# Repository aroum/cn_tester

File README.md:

# c!n tester: ProMicro-like Microcontroller Tester

## 🚀 Project Overview

The **c!n tester** is a dedicated hardware and software solution designed for automated functional testing of ProMicro-like microcontrollers (MCUs). Its primary goal is to provide a fast and reliable way to verify basic pin connectivity and functionality before deployment.

### 🚧 Current Status: Work In Progress (WIP)

The core testing logic and fundamental functionality are fully operational. However, active development is focused on improving the GUI and enhancing the overall user experience.

> [!IMPORTANT]
> **Bug Reports & Logging:**
> * **Any bug reports must be accompanied by logs.** Reports without logs cannot be diagnosed and will be closed.
> * **How to access logs:** Inside the GUI, click on the **USB connector image** at the center of the pinout visualization. This will open the log view showing real-time console outputs for both Master and Target MCUs.
> * If the application fails to start entirely, look for the `app_error.log` file created in the same directory as the executable.

## 🧱 Hardware System

The hardware consists of a custom Printed Circuit Board (PCB) housing two microcontrollers:

1. **Master MCU:** Controls the entire testing process, communicates with the host application, and manages test sequences.

2. **Target MCU:** This is the ProMicro-like microcontroller under test.

Essentially, the PCB represents a direct connection of the pins of the two microcontrollers; the same setup can be achieved using regular wires.

## 💻 Software System

**Technology Stack:**

* Python 3.10+
* PySide6 — used to create the graphical user interface (GUI).
* Nuitka — used to compile Python code into standalone executable files.
* platformio — used to compile MCU firmware.
* adafruit-nrfutil — used for flashing firmware onto microcontrollers.
* pyserial — provides communication between the computer and microcontrollers via COM ports.

All communication between the host application (software) and the MCUs is conducted via serial ports (COM ports).

Currently, there is no fully developed CLI application, but since both the Target and Master microcontrollers are connected to the computer via COM ports, you can interact with them directly using standard terminal commands.

## ⚙️ Testing Process Details

The system is designed for quick, repeatable functional checks. The Master MCU and the Target MCU communicate over dedicated lines to perform the tests.

### Test Sequence

The system uses an orchestrated handshake process to ensure reliable communication. On power-up, both MCUs send discovery messages. Once the application identifies and initializes the ports, the following sequence is performed under direct application control:

1. **Handshake & Initialization:** The application scans all COM ports (via **Auto Search** or manual selection), identifies the Master and Target, and sends an `INIT` command to synchronize them.

2. **All Pins HIGH:** The application commands both MCUs to enter the `ALL_HIGH` stage. The Target drives all pins HIGH, and the Master verifies the connectivity.

3. **All Pins LOW:** The application commands both MCUs to enter the `ALL_LOW` stage. The Target drives all pins LOW, and the Master verifies the state.

4. **Individual Pin Sequence:** The application orchestrates a per-pin sequence. It commands the Target to toggle a specific pin and then commands the Master to verify that specific pin's state. This step-by-step approach ensures maximum reliability and clear diagnostic feedback.

### Test Indicators

* **GUI Indicators:** The application provides real-time feedback for each test stage (All High, All Low, Sequence).
* **Pinout View:** A dynamic visualization shows exactly which pins passed or failed the test.
* **Master Hardware Button:** You can start the test by pressing the physical button on the Master MCU after it has been initialized by the application.

### Workflow for Testing a New Target

1. Connect the **Master MCU** to the host computer.
2. Open the **c!n tester** application.
3. Connect the new **Target MCU**.
4. Click **"Auto Search"** to automatically find and initialize both MCUs.
5. Click **"Run Test"** in the app OR press the physical **Button** on the Master MCU.
6. Wait for the test completion and observe the results in the Pinout View.
7. Insert a new Target MCU and repeat.

For now, the Master MCU is flashed manually using a uf2 file. Put the MCU into bootloader mode and copy the file to it.

## 📝 Usage Guide

The recommended and simplest way to use the application is by using the **pre-compiled binaries** available in the project's [Releases](https://github.com/aroum/cn_tester/releases/) section.

### 📦 Running Standalone Binaries (Recommended)

1. Download the executable file for your operating system from the project's [Releases](https://github.com/aroum/cn_tester/releases/) page.

2. **For Linux/macOS:** You must grant execution permissions before launching the binary:

   ```bash
   chmod +x cn_tester_app
   ```

3. **For Linux:** To allow the application to access /dev/ttyACM*, you need to add the current user to the dialout group:

   ```bash
   sudo usermod -a -G dialout $USERÍ
   ```

4. Flashing Feature Dependency: If you plan to use the target MCU flashing function, you must have the adafruit-nrfutil utility available on your system. You can ensure this in two ways:
     * Install via Pip : `pip install adafruit-nrfutil`.
     * Local Binary: Download a pre-compiled binary of [adafruit-nrfutil](https://github.com/adafruit/Adafruit_nRF52_nrfutil/releases) from its project releases and place it alongside the C!N tester app executable.
5. Launch the application:
   * **For Linux:** `./cn_tester_app_linux_x64`
   * **macOS:** `./cn_tester_app_macos_aarch64`
   * **Windows:** `cn_tester_win_x64.exe`

> [!TIP]
> To view or copy the logs for debugging, click on the **USB connector image** at the center of the pinout view in the application. See the note on [Bug Reports & Logging](#-project-overview) at the top of this document.

### 🐍 Running from Source (Development)

This method is recommended only for development or if you wish to modify the source code.

#### Prerequisites

Python 3.10 or newer.

#### Dowloand source code

```
git clone https://github.com/aroum/cn_tester.git
```

#### Install Dependencies

```
pip install -r requirements.txt
```

if you use conda:

```
conda install libpython-static
```

#### Execute the Application

```
python main.py
```

### 🏗️ Building Standalone Binaries (Nuitka)

To compile the application into a standalone executable that does not require a local Python 3.10+ environment, use the Nuitka compiler. For details, see the [nuitka documentation](https://nuitka.net/user-documentation/user-manual.html).

#### Dowloand source code

```
git clone https://github.com/aroum/cn_tester.git
```

#### Install dependencies

```
pip install -r requirements_build.txt
```

#### 🍏 macOS Compilation

##### Prerequisites

* [Xcode](https://apps.apple.com/us/app/xcode/id497799835?mt=12)
* [Homebrew](https://brew.sh)

##### Create and activate a clean environment

``` bash
brew install python@3.10 nuitka
python3.10 -m venv /tmp/cleanenv
source /tmp/cleanenv/bin/activate
# source /tmp/cleanenv/bin/activate.fish #for fish
pip install -r requirements_build.txt
```

##### Compilation

``` bash
nuitka  \
   --onefile  \
   --macos-create-app-bundle \
   --macos-app-icon=ICON_PATH \
   --macos-app-name=MACOS_APP_NAME \
   --macos-app-icon=icon/icon.png=icon/icon.png 
   --enable-plugin=pyside6  \
   --include-data-files=icon/icon.png=icon/icon.png \
   --include-data-dir=mcu_firmware=mcu_firmware \
   --include-data-files=mcu_firmware/firmware_target.hex=mcu_firmware/firmware_target.hex \
   --output-dir=build \
   --product-name="C!N Tester GUI" \
   --clean-cache=all \
   --output-filename=cn_tester_app.app \
   main.py
```

#### 🪟 Windows Compilation

##### Prerequisites

* Visual Studio C++ build tools

##### Compilation

``` bash
call "C:\Program Files\Microsoft Visual Studio\2022\BuildTools\VC\Auxiliary\Build\vcvars64.bat"

nuitka ^
  --onefile ^
  --windows-console-mode=disable ^
  --enable-plugin=pyside6 ^
  --windows-icon-from-ico=icon/icon.ico ^
  --include-data-files=icon/icon.png=icon/icon.png ^
  --include-data-dir=mcu_firmware=mcu_firmware ^
  --include-data-files=mcu_firmware/firmware_target.hex=mcu_firmware/firmware_target.hex ^
  --output-dir=build ^
  --product-name="C!N Tester GUI" ^
  --file-version=0.1.0 ^
  --clean-cache=all ^
  --output-filename=cn_tester_app.exe ^
  main.py
```

#### 🐧 Linux Compilation

##### Prerequisites

* python3-dev package
* GCC
* patchelf

##### Compilation  

``` bash
nuitka  \
   --onefile  \
   --enable-plugin=pyside6  \
   --include-data-files=icon/icon.png=icon/icon.png \
   --include-data-dir=mcu_firmware=mcu_firmware \
   --include-data-files=mcu_firmware/firmware_target.hex=mcu_firmware/firmware_target.hex \
   --output-dir=build \
   --product-name="C!N Tester GUI" \
   --clean-cache=all \
   --output-filename=cn_tester_app.bin \
   main.py
```

### 💡 Future Plans

We have several improvements planned for the upcoming sprints:

* Bluetooth Functionality Testing: Planning and implementation of test sequences to verify the basic operation of the Target MCU's Bluetooth features.
* Setup CI/CD with GitHub Actions: Implement GitHub Actions workflows for automated cross-platform compilation of the application binaries and firmware flashing.
* Add some renders of the PCB and case, as well as screenshots of the app.
* Work on the documentation.

### 🙏 Acknowledgements

A special thank you to the following community members:

Compilation & Testing: [@Rowb](https://github.com/Rowb), [@turtle-bazon](https://github.com/turtle-bazon)

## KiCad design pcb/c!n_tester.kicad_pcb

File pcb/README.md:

# Panel

In the panel folder, a 2x2 panel option is available, its size is smaller than 100x100 mm.

# Gerber files

Gerber files can be downloaded in [releases](https://github.com/aroum/cn_tester/releases).

# BOM

| Item                                                      |  Qty | Remarks                  |
| --------------------------------------------------------- | ---: | ------------------------ |
| MCU                                                       |    2 | target and master        |
| [Sockets](https://github.com/joric/nrfmicro/wiki/Sockets) | 12x4 | for MCU                  |
| SMD button 3x4x2mm                                        |    3 | for reset and start test |
| SMD resistor 0603 1-5k                                    |    1 |                          |
| SMD LED 0603                                              |    1 |                          |

[IBOM](https://htmlpreview.github.io/?https://github.com/aroum/PNCATEHO/blob/master/pcb/cn_tester/ibom/ibom.html)

You can use any sockets for the target microcontroller, but if you want to test the microcontroller without soldering I recommend spring pin headers or pogo pins (H032). When using H032 you will need to press them to ensure good contact.

![spring pin](https://private-user-images.githubusercontent.com/852547/405723092-81f82d2c-c411-478a-a34d-f9249b987f54.jpg?jwt=eyJ0eXAiOiJKV1QiLCJhbGciOiJIUzI1NiJ9.eyJpc3MiOiJnaXRodWIuY29tIiwiYXVkIjoicmF3LmdpdGh1YnVzZXJjb250ZW50LmNvbSIsImtleSI6ImtleTUiLCJleHAiOjE3Nzc3OTA3NzEsIm5iZiI6MTc3Nzc5MDQ3MSwicGF0aCI6Ii84NTI1NDcvNDA1NzIzMDkyLTgxZjgyZDJjLWM0MTEtNDc4YS1hMzRkLWY5MjQ5Yjk4N2Y1NC5qcGc_WC1BbXotQWxnb3JpdGhtPUFXUzQtSE1BQy1TSEEyNTYmWC1BbXotQ3JlZGVudGlhbD1BS0lBVkNPRFlMU0E1M1BRSzRaQSUyRjIwMjYwNTAzJTJGdXMtZWFzdC0xJTJGczMlMkZhd3M0X3JlcXVlc3QmWC1BbXotRGF0ZT0yMDI2MDUwM1QwNjQxMTFaJlgtQW16LUV4cGlyZXM9MzAwJlgtQW16LVNpZ25hdHVyZT02YzVjMjYwZTYzMjE3NDg4OWUwNWE2OTkxNzcyZDhjNjZiNmZlYmY0Y2U3OTIxMTYwZDI5NGEzMmY4NDJhYjU5JlgtQW16LVNpZ25lZEhlYWRlcnM9aG9zdCZyZXNwb25zZS1jb250ZW50LXR5cGU9aW1hZ2UlMkZqcGVnIn0.y77NcWKNbWCfdUeS-7dsdKGYXl6NTeUTuKWItCsfQM0)

Thanks to [@ShyPsy](https://github.com/ShyPsy) for choosing and testing suitable pogo pins.

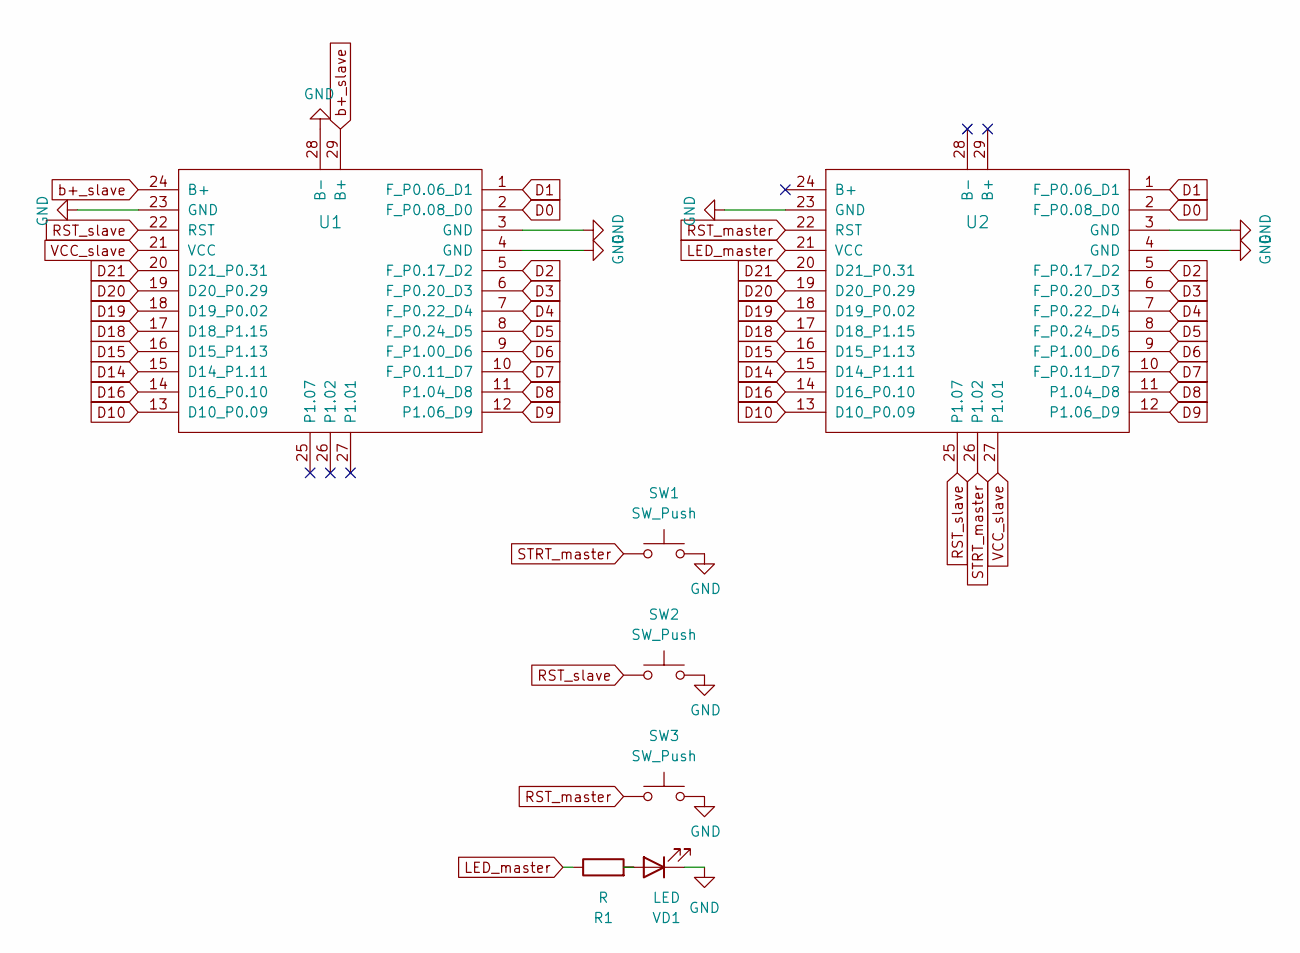
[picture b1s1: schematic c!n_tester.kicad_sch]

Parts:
R1: R
SW1, SW2, SW3: SW_Push
U1, U2: ProMicro_r; ProMicro_cutout
VD1: LED

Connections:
D0: U1.2 (F_P0.08_D0), U2.2 (F_P0.08_D0)
D1: U1.1 (F_P0.06_D1), U2.1 (F_P0.06_D1)
D2: U1.5 (F_P0.17_D2), U2.5 (F_P0.17_D2)
D3: U1.6 (F_P0.20_D3), U2.6 (F_P0.20_D3)
D4: U1.7 (F_P0.22_D4), U2.7 (F_P0.22_D4)
D5: U1.8 (F_P0.24_D5), U2.8 (F_P0.24_D5)
D6: U1.9 (F_P1.00_D6), U2.9 (F_P1.00_D6)
D7: U1.10 (F_P0.11_D7), U2.10 (F_P0.11_D7)
D8: U1.11 (P1.04_D8), U2.11 (P1.04_D8)
D9: U1.12 (P1.06_D9), U2.12 (P1.06_D9)
D10: U1.13 (D10_P0.09), U2.13 (D10_P0.09)
D14: U1.15 (D14_P1.11), U2.15 (D14_P1.11)
D15: U1.16 (D15_P1.13), U2.16 (D15_P1.13)
D16: U1.14 (D16_P0.10), U2.14 (D16_P0.10)
D18: U1.17 (D18_P1.15), U2.17 (D18_P1.15)
D19: U1.18 (D19_P0.02), U2.18 (D19_P0.02)
D20: U1.19 (D20_P0.29), U2.19 (D20_P0.29)
D21: U1.20 (D21_P0.31), U2.20 (D21_P0.31)
GND: SW1.2, SW2.2, SW3.2, U1.3 (GND), U1.4 (GND), U1.23 (GND), U1.28 (B-), U2.3 (GND), U2.4 (GND), U2.23 (GND), VD1.1 (K)
LED_master: R1.1, U2.21 (VCC)
unnamed: R1.2, VD1.2 (A)
RST_master: SW3.1, U2.22 (RST)
RST_slave: SW2.1, U1.22 (RST), U2.25 (P1.07)
STRT_master: SW1.1, U2.26 (P1.02)
VCC_slave: U1.21 (VCC), U2.27 (P1.01)
b+_slave: U1.24 (B+), U1.29 (B+)

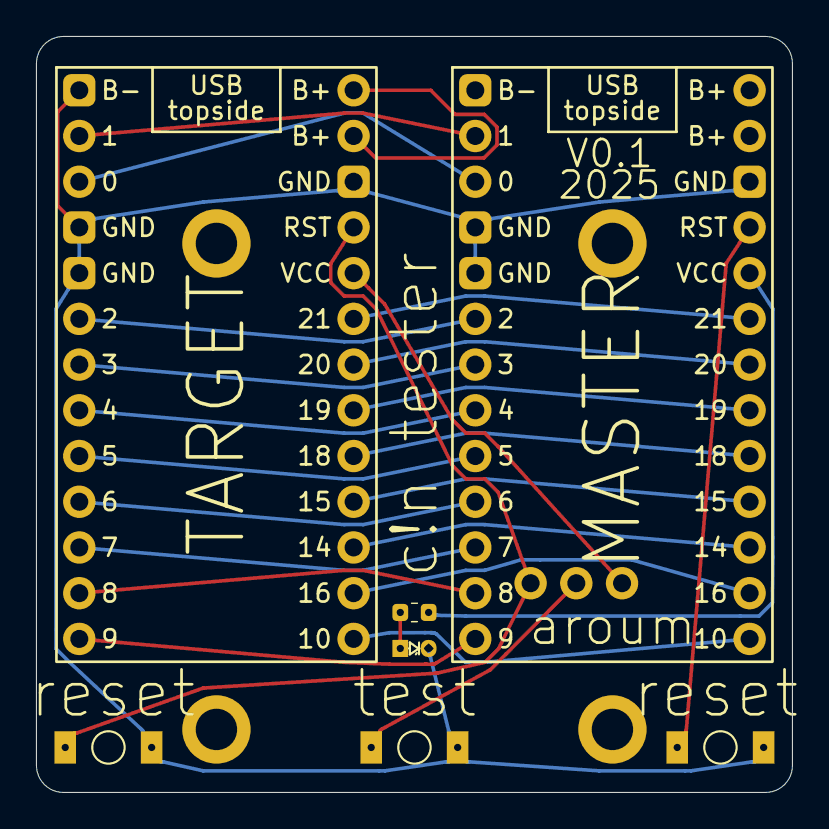
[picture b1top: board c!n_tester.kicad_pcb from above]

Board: 2 copper layers, 42.0 x 42.0 mm, 11 parts (1 on the bottom side), 26 nets.

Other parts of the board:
H1, H2, H3, H4: MountingHole; mountingHole_plate

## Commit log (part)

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2025-11-07 Initial project structure and core files added
    Added application source files, firmware, hardware case, and PCB design files. Updated README with detailed documentation and usage instructions. Included .gitignore for common build and environment 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
2025-11-08 Add dark mode app screenshot to README
    Inserted a new screenshot (app_screenshot_win_dark.png) into the README to showcase the application's appearance in Windows dark mode.
2025-11-08 Update README with execution and flashing instructions
    Corrected instructions and formatting for application execution and flashing dependencies.
2025-11-08 Update output filename for macOS and Windows builds
2025-11-18 Fix line continuation for Nuitka build on Windows
    Replaces backslashes with backticks for line continuation in the Nuitka build command on Windows to ensure proper execution in PowerShell.
2025-11-18 Add Nuitka auto-download flag to build workflow
    Adds the --assume-yes-for-downloads flag to the Nuitka build step in the GitHub Actions workflow to automatically confirm downloads, improving CI automation.
2026-05-03 add info about pogo pins
2026-05-06 Refactor pin state handling in main loop
    Refactor state machine logic to use a buffer for current pin levels and improve error reporting for dynamic pin states.
2026-05-06 Revert "Refactor pin state handling in main loop"
    This reverts commit e9a28d489d1da55b9b23fc83d77d5c65b24e0e57.
2026-05-07 Cache pin reads and inline pin-printing
    Introduce a currentLevels scan buffer to avoid repeated digitalRead calls each loop and remove the printDynamicPinsByLevel helper. Inline printing of LOW/HIGH pin lists where needed, rename highIdx t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
2026-05-07 Add PlatformIO CI and rename build workflow
    Rename existing .github/workflows/build.yml to build_app.yml and add a new .github/workflows/build_fw.yml to run PlatformIO CI for the Supermini firmware. The new workflow triggers on push and pull_r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
2026-05-08 Add nice!nano boards and CI for firmwares
    Add nice!nano board definitions and variant sources for both master_firmware and target_firmware (boards/nicenano.json, variant.cpp, variant.h). Update each platformio.ini to use env supermini, set s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
2026-05-08 Use P0_xx/P1_xx pin macro names
    Replace numeric PIN_### macros with explicit P0_xx / P1_xx names in nicenano variant headers for both master and target firmware. This clarifies port/bit mapping (P0.02..P0.31 and P1.00..P1.15) and s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
2026-05-08 Update workflows and increase hold timings
    Rename CI workflow entries and tighten firmware triggers, and lengthen MCU hold timings.
    - .github/workflows/build_app.yml: changed workflow name to "Build App (Nuitka)".
    - .github/workflows/build_fw.yml: renamed to "Build Firmware (PlatformIO for n!n_v2)" and updated triggers to manual dispatch and tag-based pushes (v*), replacing the previous push/pull_request trigg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
    - mcu_firmwares/target_firmware/src/main.cpp: increased HOLD_ALL_HIGH_MS and HOLD_ALL_LOW_MS from 1000ms to 2500ms to give the master more time to sample during the protocol.
    These changes make firmware builds run on explicit releases/manual runs and improve timing reliability fo
2026-05-10 Add MCU handshake, auto-search and protocol control
    Implement end-to-end handshake and command-driven test orchestration: add serial port auto-discovery (discover_mcu_ports) and an "Auto Search" UI button that initializes Master/Target combos and rest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
2026-05-10 Sync INIT/READY flow and UI readiness handling
    Make the UI and firmwares more robust around INIT/READY/start sequencing. UI: add _master_ready/_target_ready and _last_action flags, send INIT to both devices on Run, wait for both READY before issu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
2026-05-17 update mcu fw
2026-05-17 fix build
2026-05-17 fix SS pin
2026-05-17 fix lib_deps
2026-05-17 fix lib_deps 2
2026-06-02 app: fix pin name
2026-06-16 case: add target board holder
